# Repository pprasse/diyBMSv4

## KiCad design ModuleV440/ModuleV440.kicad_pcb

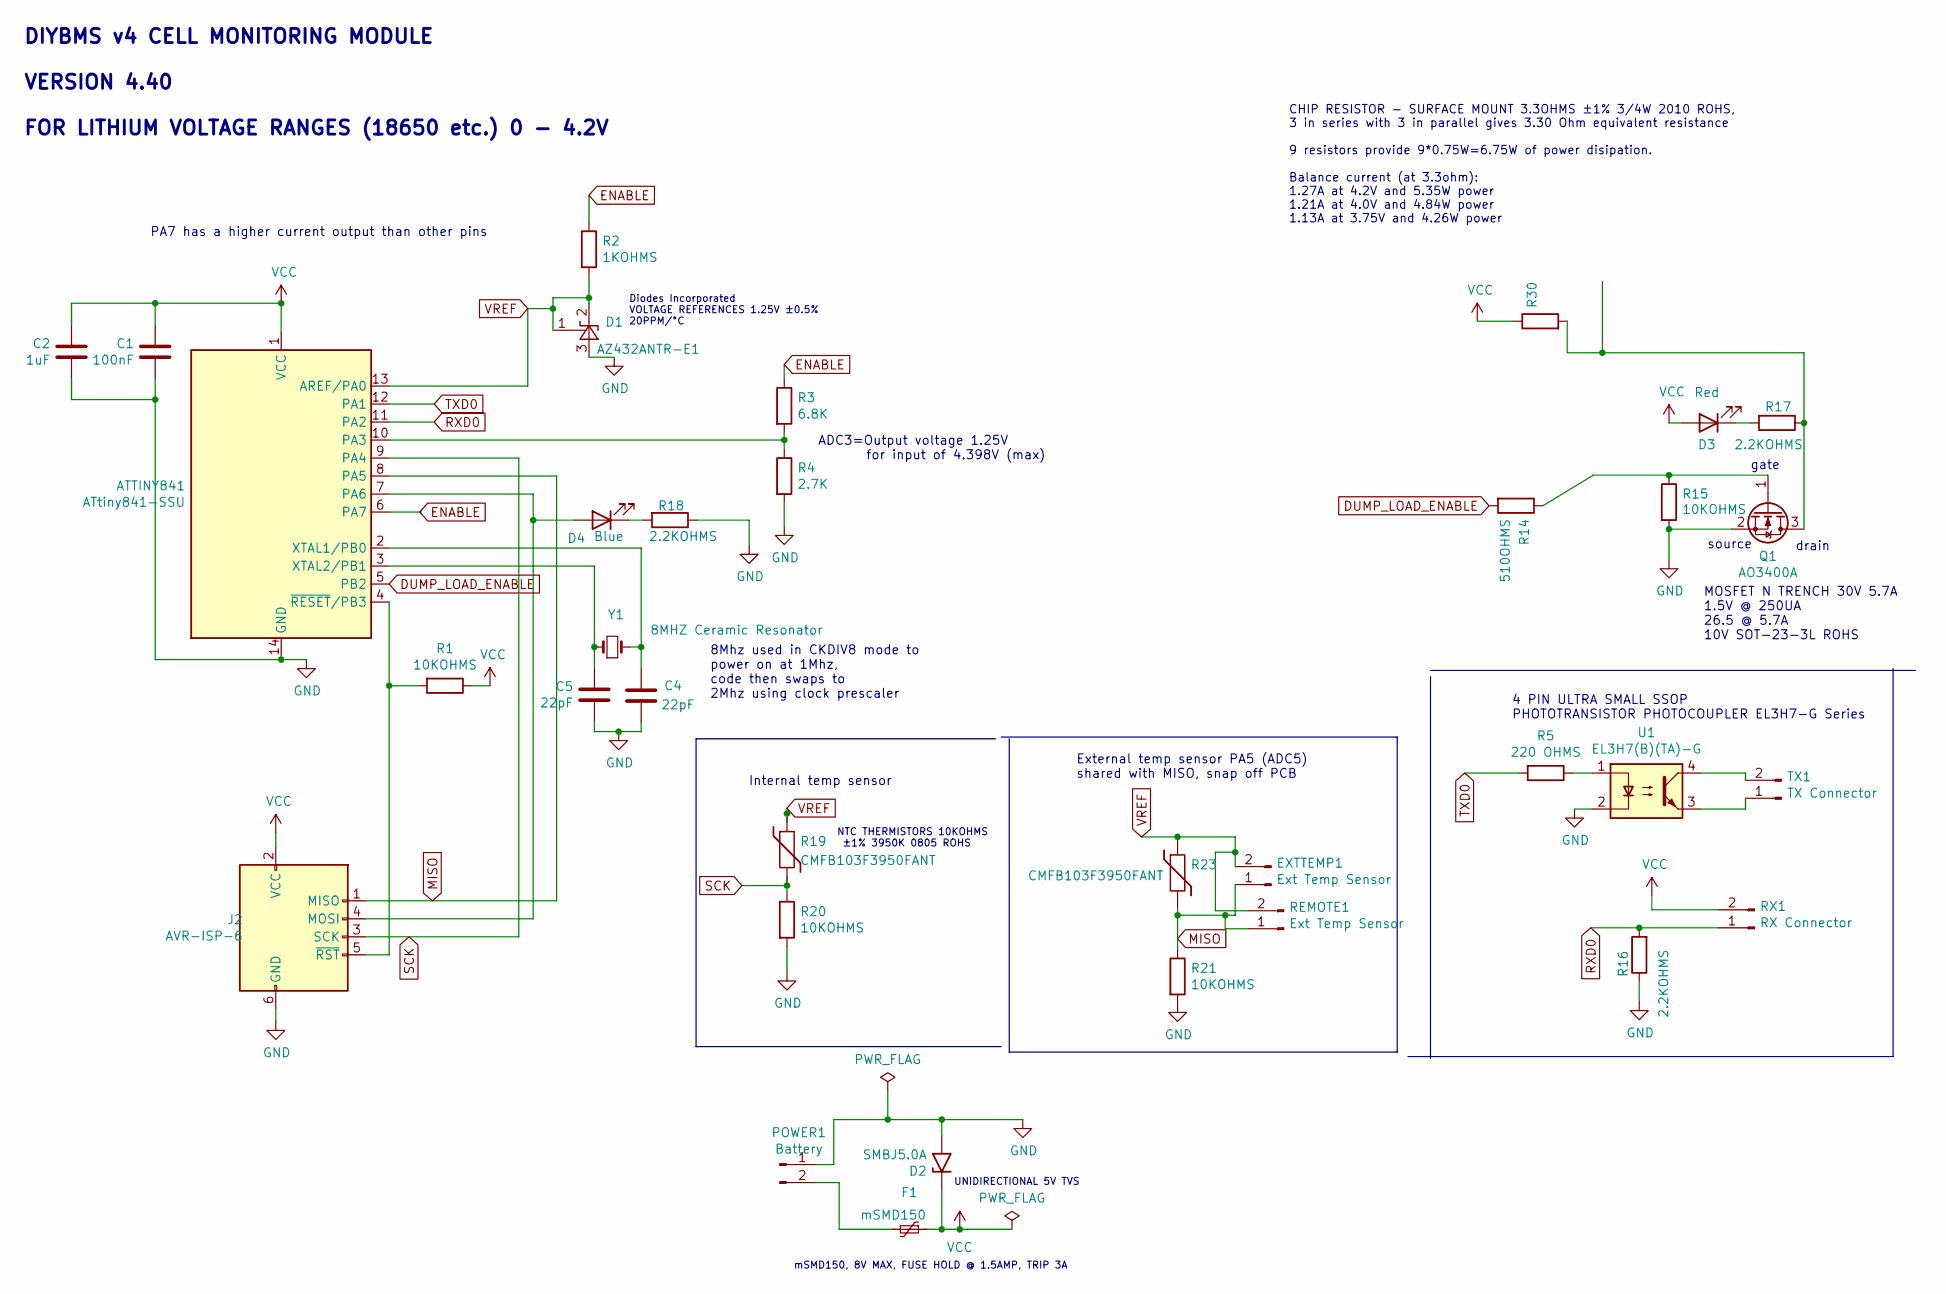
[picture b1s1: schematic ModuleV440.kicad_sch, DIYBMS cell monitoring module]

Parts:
ATTINY841: ATtiny841-SSU; SOIC-14_3.9x8.7mm_P1.27mm; LCSCStockCode C219103
C1: 100nF; C_0805_2012Metric; PartNumber CC0805KRX7R9BB104; LCSCStockCode C49678
C2: 1uF; C_0805_2012Metric; PartNumber CL21B105KBFNNNE; LCSCStockCode C28323
C4, C5: 22pF; C_0805_2012Metric; PartNumber CL21C220JBANNNC; LCSCStockCode C1804
D1: AZ432ANTR-E1; SOT-23; PartNumber AZ432ANTR-E1; LCSCStockCode C84139
D2: SMBJ5.0A; D_SMB; LCSCStockCode C440263
D3: Red; LED_0805_2012Metric; PartNumber 2012HRK-620D; LCSCStockCode C84256
D4: Blue; LED_0805_2012Metric; PartNumber Blue LED; LCSCStockCode C2293
EXTTEMP1: Ext Temp Sensor; JST_PH_S2B-PH-K_1x02_P2.00mm_Horizontal; PartNumber S2B-PH-K(LF)(SN); LCSCStockCode C265016
F1: mSMD150; Fuse_1812_4532Metric; PartNumber mSMD150; LCSCStockCode C70121
J2: AVR-ISP-6; Pin_Header_Straight_2x03_Pitch2.54mm; LCSCStockCode C65114
POWER1: Battery; JST_PH_S2B-PH-K_1x02_P2.00mm_Horizontal; PartNumber S2B-PH-K(LF)(SN); LCSCStockCode C265016
Q1: AO3400A; SOT-23; PartNumber AO3400A; LCSCStockCode C20917
R1, R15, R20, R21: 10KOHMS; R_0805_2012Metric; PartNumber 0805W8F1002T5E; LCSCStockCode C17414
R2: 1KOHMS; R_0805_2012Metric; PartNumber 0805W8F1001T5E; LCSCStockCode C17513
R3: 6.8K; R_0805_2012Metric; PartNumber 0805W8F6801T5E; LCSCStockCode C17772
R4: 2.7K; R_0805_2012Metric; PartNumber 0805W8F2701T5E; LCSCStockCode C17530
R5: 220 OHMS; R_0805_2012Metric; PartNumber 0805W8F2200T5E; LCSCStockCode C17557
R14: 510OHMS; R_0805_2012Metric; PartNumber 0805W8F5100T5E; LCSCStockCode C17734
R16, R17, R18: 2.2KOHMS; R_0805_2012Metric; PartNumber 0805W8F2201T5E; LCSCStockCode C17520
R19, R23: CMFB103F3950FANT; R_0805_2012Metric; PartNumber CMFB103F3950FANT; LCSCStockCode C51597
R30: 3.3OHM 3/4W; R_Radial_Power_L13.0mm_W9.0mm_P5.00mm; PartNumber SQMW53R3J
REMOTE1: Ext Temp Sensor; PinHeader_1x02_P2.54mm_Vertical
RX1: RX Connector; JST_PH_S2B-PH-K_1x02_P2.00mm_Horizontal; PartNumber S2B-PH-K(LF)(SN); LCSCStockCode C265016
TX1: TX Connector; JST_PH_S2B-PH-K_1x02_P2.00mm_Horizontal; PartNumber S2B-PH-K(LF)(SN); LCSCStockCode C265016
U1: EL3H7(B)(TA)-G; SOP-4_4.4x2.6mm_P1.27mm; PartNumber EL3H7(B)(TA)-G; LCSCStockCode C32565
Y1: 8MHZ Ceramic Resonator; Crystal_SMD_5032-2pin_5.0x3.2mm; PartNumber X50328MSB2GI; LCSCStockCode C115962

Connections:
DUMP_LOAD_ENABLE: ATTINY841.5 (PB2), R14.2
ENABLE: ATTINY841.6 (PA7), R2.1, R3.1
GND: ATTINY841.14 (GND), C1.2, C2.2, C4.2, C5.2, D1.3 (A), D2.2 (A2), J2.6 (GND), POWER1.1, Q1.2 (S), R4.2, R15.2, R16.1, R18.1, R20.2, R21.2, U1.2
MISO: ATTINY841.8 (PA5), EXTTEMP1.1, J2.1 (MISO), R21.1, R23.2, REMOTE1.1
unnamed: ATTINY841.10 (PA3), R3.2, R4.1
unnamed: ATTINY841.7 (PA6), D4.2 (A), J2.4 (MOSI)
unnamed: ATTINY841.2 (XTAL1/PB0), C4.1, Y1.2
unnamed: ATTINY841.3 (XTAL2/PB1), C5.1, Y1.1
unnamed: ATTINY841.4 (~RESET/PB3), J2.5 (~RST), R1.2
unnamed: D3.1 (K), R17.2
unnamed: D4.1 (K), R18.2
unnamed: F1.2, POWER1.2
unnamed: Q1.3 (D), R17.1, R30.2
unnamed: Q1.1 (G), R14.1, R15.1
unnamed: R5.1, U1.1
unnamed: TX1.1, U1.3
unnamed: TX1.2, U1.4
RXD0: ATTINY841.11 (PA2), R16.2, RX1.1
SCK: ATTINY841.9 (PA4), J2.3 (SCK), R19.2, R20.1
TXD0: ATTINY841.12 (PA1), R5.2
VCC: ATTINY841.1 (VCC), C1.1, C2.1, D2.1 (A1), D3.2 (A), F1.1, J2.2 (VCC), R1.1, R30.1, RX1.2
VREF: ATTINY841.13 (AREF/PA0), D1.1 (FB), D1.2 (K), EXTTEMP1.2, R2.2, R19.1, R23.1, REMOTE1.2

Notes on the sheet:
PA7 has a higher current output than other pins
CHIP RESISTOR - SURFACE MOUNT 3.3OHMS ±1% 3/4W 2010 ROHS, 3 in series with 3 in parallel gives 3.30 Ohm equivalent resistance 9 resistors provide 9*0.75W=6.75W of power disipation. Balance current (at 3.3ohm): 1.27A at 4.2V and 5.35W power 1.21A at 4.0V and 4.84W power 1.13A at 3.75V and 4.26W power
drain
mSMD150, 8V MAX, FUSE HOLD @ 1.5AMP, TRIP 3A
8Mhz used in CKDIV8 mode to power on at 1Mhz, code then swaps to 2Mhz using clock prescaler
4 PIN ULTRA SMALL SSOP PHOTOTRANSISTOR PHOTOCOUPLER EL3H7-G Series
ADC3=Output voltage 1.25V for input of 4.398V (max)
Diodes Incorporated VOLTAGE REFERENCES 1.25V ±0.5% 20PPM/°C
source
DIYBMS v4 CELL MONITORING MODULE VERSION 4.40 FOR LITHIUM VOLTAGE RANGES (18650 etc.) 0 - 4.2V
UNIDIRECTIONAL 5V TVS
NTC THERMISTORS 10KOHMS ±1% 3950K 0805 ROHS
gate
Internal temp sensor
External temp sensor PA5 (ADC5) shared with MISO, snap off PCB
MOSFET N TRENCH 30V 5.7A 1.5V @ 250UA 26.5 @ 5.7A 10V SOT-23-3L ROHS

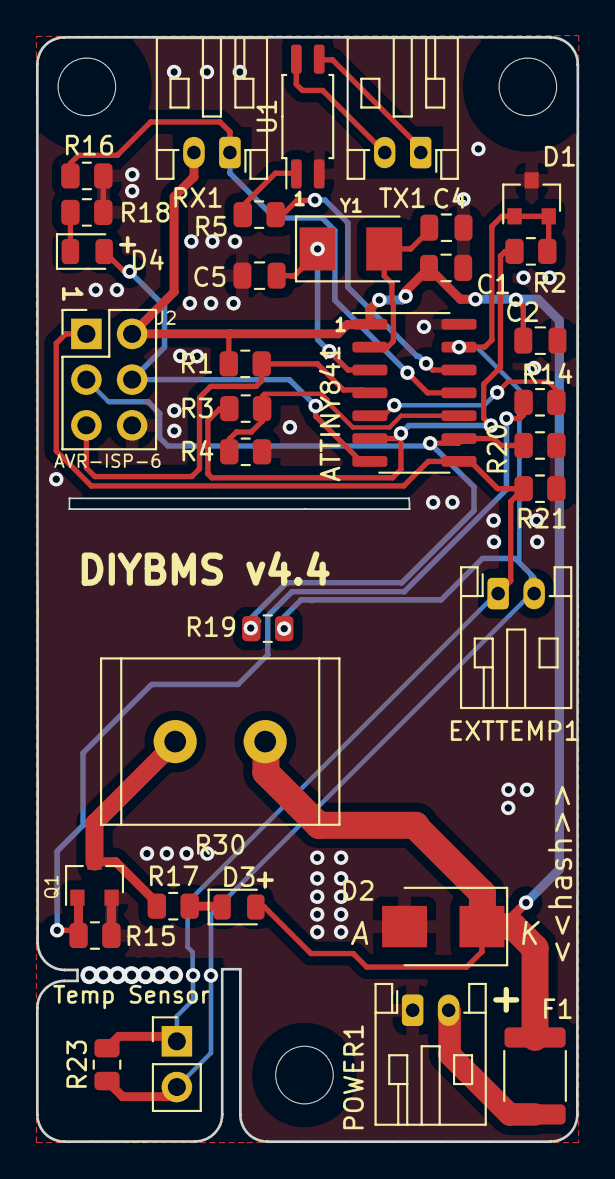
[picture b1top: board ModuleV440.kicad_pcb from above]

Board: 2 copper layers, 30.0 x 61.3 mm, 34 parts (0 on the bottom side), 22 nets.

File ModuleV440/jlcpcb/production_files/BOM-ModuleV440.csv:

Comment,Designator,Footprint,LCSC
8MHZ Ceramic Resonator,Y1,Crystal_SMD_5032-2pin_5.0x3.2mm,C115962
3.3OHM 3/4W,R30,R_Radial_Power_L13.0mm_W9.0mm_P5.00mm,C1366653
10KOHMS,"R1,R15,R20,R21",R_0805_2012Metric,C17414
1KOHMS,R2,R_0805_2012Metric,C17513
2.2KOHMS,"R16,R17,R18",R_0805_2012Metric,C17520
2.7K,R4,R_0805_2012Metric,C17530
220 OHMS,R5,R_0805_2012Metric,C17557
510OHMS,R14,R_0805_2012Metric,C17734
6.8K,R3,R_0805_2012Metric,C17772
22pF,"C4,C5",C_0805_2012Metric,C1804
AO3400A,Q1,SOT-23,C20917
ATtiny841-SSU,ATTINY841,SOIC-14_3.9x8.7mm_P1.27mm,C219103
Blue,D4,LED_0805_2012Metric,C2293
Ext Temp Sensor,"EXTTEMP1,POWER1,RX1,TX1",JST_PH_S2B-PH-K_1x02_P2.00mm_Horizontal,C265016
1uF,C2,C_0805_2012Metric,C28323
EL3H7(B)(TA)-G,U1,SOP-4_4.4x2.6mm_P1.27mm,C32565
SMBJ5.0A,D2,D_SMB,C440263
100nF,C1,C_0805_2012Metric,C49678
CMFB103F3950FANT,"R19,R23",R_0805_2012Metric,C51597
AVR-ISP-6,J2,Pin_Header_Straight_2x03_Pitch2.54mm,C65114
mSMD150,F1,Fuse_1812_4532Metric,C70121
AZ432ANTR-E1,D1,SOT-23,C84139
Red,D3,LED_0805_2012Metric,C84256
Ext Temp Sensor,REMOTE1,PinHeader_1x02_P2.54mm_Vertical,

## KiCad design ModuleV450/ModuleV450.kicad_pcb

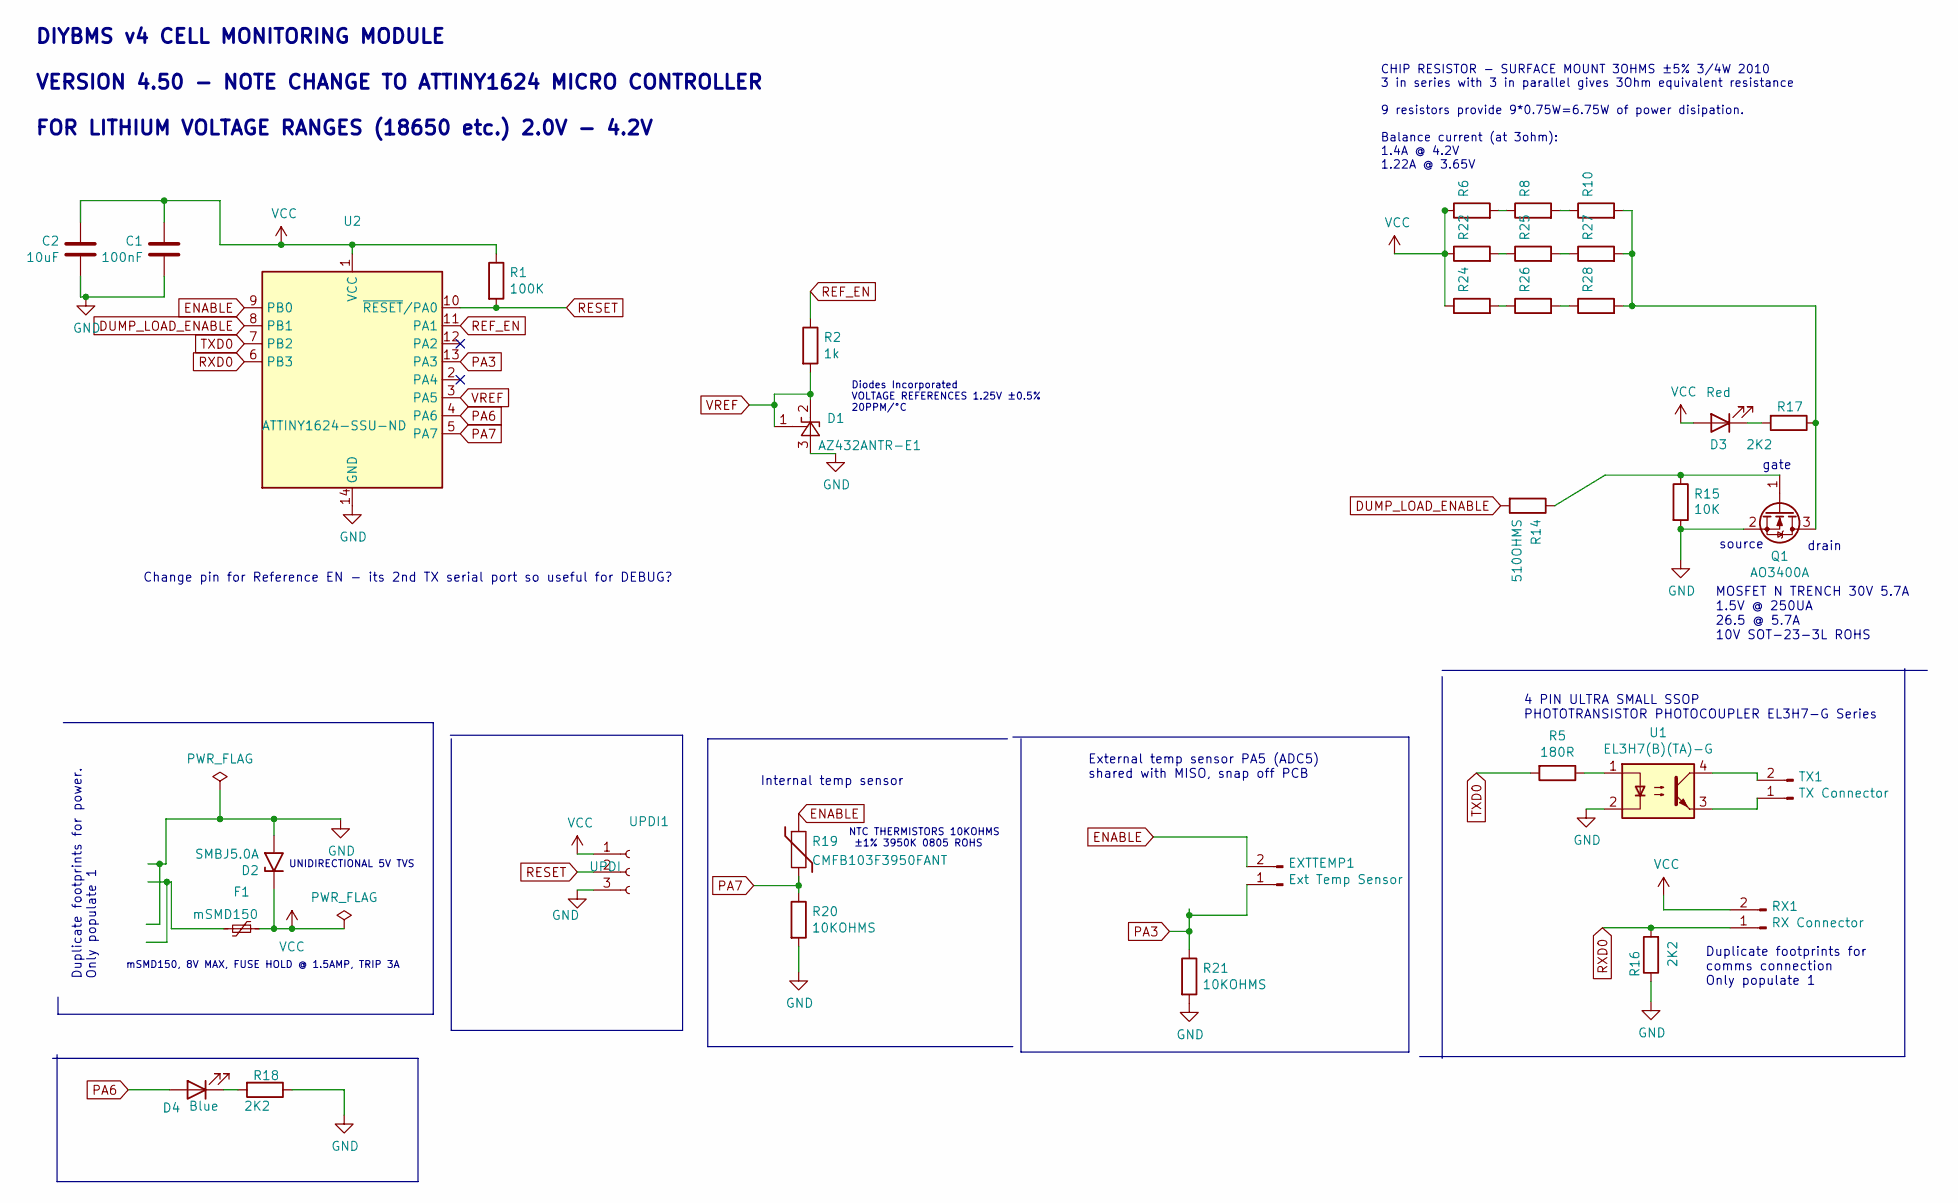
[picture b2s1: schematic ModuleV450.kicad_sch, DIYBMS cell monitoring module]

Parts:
C1: 100nF; C_0805_2012Metric; PartNumber CC0805KRX7R9BB104; LCSCStockCode C49678
C2: 10uF; C_0805_2012Metric; PartNumber CL21A106KAYNNNE; LCSCStockCode C15850
D1: AZ432ANTR-E1; SOT-23; PartNumber AZ432ANTR-E1; LCSCStockCode C84139
D2: SMBJ5.0A; D_SMB; LCSCStockCode C440263
D3: Red; LED_0805_2012Metric; PartNumber NCD0805R1; LCSCStockCode C84256
D4: Blue; LED_0603_1608Metric; PartNumber 19-217/GHC-YR1S2/3T; LCSCStockCode C72043
EXTTEMP1: Ext Temp Sensor; PinHeader_1x02_P2.54mm_Vertical; PartNumber S2B-PH-K(LF)(SN); LCSCStockCode C265016
F1: mSMD150; Fuse_1812_4532Metric; PartNumber mSMD150; LCSCStockCode C70121
Q1: AO3400A; SOT-23; PartNumber AO3400A; LCSCStockCode C347475
R1: 100K; R_0805_2012Metric; PartNumber 0805W8F1003T5E; LCSCStockCode C149504
R2: 1k; R_0805_2012Metric; PartNumber 0805W8F1001T5E; LCSCStockCode C17513
R5: 180R; R_0805_2012Metric; PartNumber 0805W8F1800T5E; LCSCStockCode C25270
R6, R8, R10, R22, R24, R25, R26, R27, R28: 3R; R_2010_5025Metric; PartNumber 201007J030JT4E; LCSCStockCode C474300
R14: 510OHMS; R_0805_2012Metric; PartNumber 0805W8F5100T5E; LCSCStockCode C17734
R15: 10K; R_0805_2012Metric; PartNumber 0805W8F1002T5E; LCSCStockCode C17414
R16, R17, R18: 2K2; R_0805_2012Metric; PartNumber 0805W8F2201T5E; LCSCStockCode C17520
R19: CMFB103F3950FANT; R_0805_2012Metric; PartNumber CMFB103F3950FANT; LCSCStockCode C51597
R20, R21: 10KOHMS; R_0805_2012Metric; PartNumber 0805W8F1002T5E; LCSCStockCode C17414
RX1: RX Connector; PinHeader_1x02_P2.54mm_Horizontal; PartNumber PZ254R-11-02P; LCSCStockCode C492410
TX1: TX Connector; PinHeader_1x02_P2.54mm_Horizontal; PartNumber PZ254R-11-02P; LCSCStockCode C492410
U1: EL3H7(B)(TA)-G; SOP-4_4.4x2.6mm_P1.27mm; PartNumber EL3H7(B)(TA)-G; LCSCStockCode C32565
U2: ATTINY1624-SSU-ND; SOIC-14_3.9x8.7mm_P1.27mm; PartNumber ATTINY1624-SSU-ND; LCSCStockCode C3237666
UPDI1: UPDI; PinSocket_1x03_P2.54mm_Vertical

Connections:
DUMP_LOAD_ENABLE: R14.2, U2.8 (PB1)
ENABLE: EXTTEMP1.2, R19.1, U2.9 (PB0)
GND: C1.2, C2.2, D1.3 (A), D2.2 (A2), Q1.2 (S), R15.2, R16.1, R18.1, R20.2, R21.2, U1.2, U2.14 (GND), UPDI1.3
unnamed: D3.1 (K), R17.2
unnamed: D4.1 (K), R18.2
unnamed 5: Q1.3 (D), R10.2, R17.1, R27.2, R28.2; also elsewhere on the board
unnamed: Q1.1 (G), R14.1, R15.1
unnamed: R5.1, U1.1
unnamed: R6.2, R8.1
unnamed: R8.2, R10.1
unnamed: R22.2, R25.1
unnamed: R24.2, R26.1
unnamed: R25.2, R27.1
unnamed: R26.2, R28.1
unnamed: TX1.1, U1.3
unnamed: TX1.2, U1.4
PA3: EXTTEMP1.1, R21.1, U2.13 (PA3)
PA6: D4.2 (A), U2.4 (PA6)
PA7: R19.2, R20.1, U2.5 (PA7)
REF_EN: R2.1, U2.11 (PA1)
RESET: R1.2, U2.10 (~RESET/PA0), UPDI1.2
RXD0: R16.2, RX1.1, U2.6 (PB3)
TXD0: R5.2, U2.7 (PB2)
VCC: C1.1, C2.1, D2.1 (A1), D3.2 (A), F1.1, R1.1, R6.1, R22.1, R24.1, RX1.2, U2.1 (VCC), UPDI1.1; also elsewhere on the board
VREF: D1.1 (FB), D1.2 (K), R2.2, U2.3 (PA5)

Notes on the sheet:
drain
4 PIN ULTRA SMALL SSOP PHOTOTRANSISTOR PHOTOCOUPLER EL3H7-G Series
gate
UNIDIRECTIONAL 5V TVS
MOSFET N TRENCH 30V 5.7A 1.5V @ 250UA 26.5 @ 5.7A 10V SOT-23-3L ROHS
External temp sensor PA5 (ADC5) shared with MISO, snap off PCB
Change pin for Reference EN - its 2nd TX serial port so useful for DEBUG?
DIYBMS v4 CELL MONITORING MODULE VERSION 4.50 - NOTE CHANGE TO ATTINY1624 MICRO CONTROLLER FOR LITHIUM VOLTAGE RANGES (18650 etc.) 2.0V - 4.2V
source
Duplicate footprints for comms connection Only populate 1
NTC THERMISTORS 10KOHMS ±1% 3950K 0805 ROHS
CHIP RESISTOR - SURFACE MOUNT 3OHMS ±5% 3/4W 2010 3 in series with 3 in parallel gives 3Ohm equivalent resistance 9 resistors provide 9*0.75W=6.75W of power disipation. Balance current (at 3ohm): 1.4A @ 4.2V 1.22A @ 3.65V
mSMD150, 8V MAX, FUSE HOLD @ 1.5AMP, TRIP 3A
Internal temp sensor
Diodes Incorporated VOLTAGE REFERENCES 1.25V ±0.5% 20PPM/°C
Duplicate footprints for power. Only populate 1

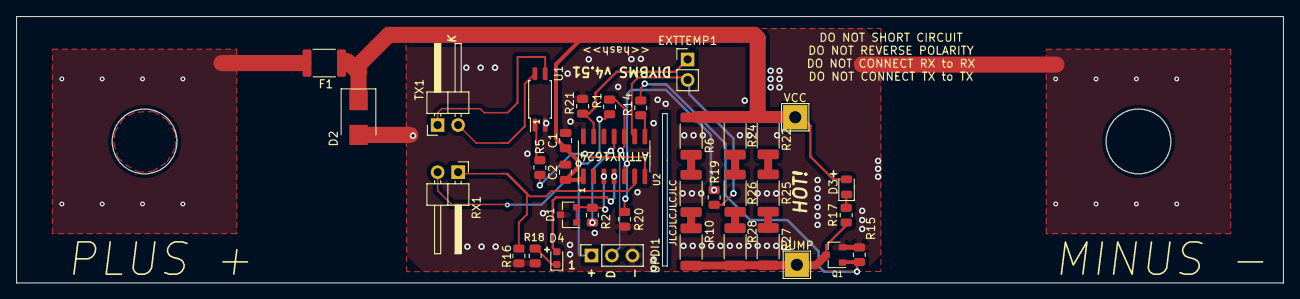
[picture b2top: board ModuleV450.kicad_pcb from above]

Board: 2 copper layers, 157.0 x 33.0 mm, 36 parts (0 on the bottom side), 25 nets.

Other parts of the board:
DUMP: TestPoint_THTPad_3.0x3.0mm_Drill1.5mm
VCC: TestPoint_THTPad_3.0x3.0mm_Drill1.5mm

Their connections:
unnamed 5: DUMP.1; also elsewhere on the board
VCC: VCC.1; also elsewhere on the board

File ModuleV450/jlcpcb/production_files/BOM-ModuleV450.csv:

Comment,Designator,Footprint,LCSC
100K,R1,R_0805_2012Metric,C149504
10uF,C2,C_0805_2012Metric,C15850
3R,"R10,R22,R24,R25,R26,R27,R28,R6,R8",R_2010_5025Metric,C159239
10K,"R15,R20,R21",R_0805_2012Metric,C17414
1k,R2,R_0805_2012Metric,C17513
2K2,"R16,R17,R18",R_0805_2012Metric,C17520
510OHMS,R14,R_0805_2012Metric,C17734
180R,R5,R_0805_2012Metric,C25270
EL3H7(B)(TA)-G,U1,SOP-4_4.4x2.6mm_P1.27mm,C32565
AO3400A,Q1,SOT-23,C347475
SMBJ5.0A,D2,D_SMB,C440263
AZ432ANTR-E1,D1,SOT-23,C460576
RX Connector,"RX1,TX1",PinHeader_1x02_P2.54mm_Horizontal,C492410
100nF,C1,C_0805_2012Metric,C49678
UPDI,UPDI1,PinSocket_1x03_P2.54mm_Vertical,C5116529
CMFB103F3950FANT,R19,R_0805_2012Metric,C51597
ATTINY1624-SSU-ND,U2,SOIC-14_3.9x8.7mm_P1.27mm,C5160891
mSMD150,F1,Fuse_1812_4532Metric,C70121
Blue,D4,LED_0603_1608Metric,C72043
Red,D3,LED_0805_2012Metric,C84256

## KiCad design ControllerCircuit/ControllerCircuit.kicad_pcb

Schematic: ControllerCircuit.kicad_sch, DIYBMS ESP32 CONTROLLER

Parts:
C1, C2, C6, C8, C9: 100nF; C_0805_2012Metric; LCSCStockCode C49678
C3, C4: 22uF 6.3V; CP_EIA-3216-18_Kemet-A_Pad1.58x1.35mm_HandSolder; PartNumber TC212A226K006Y; LCSCStockCode C110786
C5: 22uF; C_1206_3216Metric; PartNumber CL31A226KPHNNNE; LCSCStockCode C5672
C7, C11: 1uF; C_0805_2012Metric; LCSCStockCode C28323
C10, C13: 1uF; C_0805_2012Metric; PartNumber CL21B105KBFNNNE; LCSCStockCode C28323
C12: 0.1uF-100V; C_0805_2012Metric; PartNumber C0805C104K1RECAUTO; LCSCStockCode C696367
C14: 100nF; C_0805_2012Metric; PartNumber CC0805KRX7R9BB104; LCSCStockCode C49678
D1: RGB; LED_RGB_5050-6; LCSCStockCode C219409
D2, D5: LL4148; D_MiniMELF; PartNumber LL4148; LCSCStockCode C9808
D3, D4: YELLOW LED; LED_0603_1608Metric_Pad1.05x0.95mm_HandSolder; LCSCStockCode C72038
D6: MHPC3528CRGBCT; LED_MHPC3528CRGBCT
D8: NUP2105LT1G; SOT-23; LCSCStockCode C2976509
F1: Fuse, 1.85A; Fuse_2920_7451Metric; PartNumber TLC-LSMD185; LCSCStockCode C262041
J1, J4, J7, J12: ScrewTerminal; Terminal-Block_3.81_4P_LCSC_C395880; LCSCStockCode C395880
J2, J3: ScrewTerminal3Pin; Terminal-Block_5.0mm_3P-LCSC_C395850; LCSCStockCode C395850
J5: ScrewTerminal; Terminal-Block_3.81_2P-LCSC_C395878; LCSCStockCode C395878
J8: 2x3 2.54mm IDC Connectors; PinHeader_2x03_P2.54mm_Vertical; LCSCStockCode C132438
J9: Shunt; Terminal-Block_3.81_4P_LCSC_C395880; LCSCStockCode C395880
J10: Conn_01x02_Female; PinHeader_1x02_P2.54mm_Horizontal; LCSCStockCode C376120
J14: Unused header; PinHeader_1x07_P2.54mm_Vertical
J15: Molex 0472192001; 0472192001; Manufacturer_Part_Number 0472192001; Mouser Part Number N/A
JP1: OptTermination; SolderJumper-2_P1.3mm_Bridged_Pad1.0x1.5mm
JP4: OptTermination; SolderJumper-2_P1.3mm_Bridged_RoundedPad1.0x1.5mm
K1, K2: SRD-05VDC-SL-C; RELAY_SRD-05VDC-SL-C; PartNumber SRD-05VDC-SL-C; LCSCStockCode C35449
LCD1: LCD; TFTSPI_2_8_240x320_TOUCH; LCSCStockCode C52711/C358718
Q1, Q2, Q4: AO3400A; SOT-23; PartNumber AO3400A; LCSCStockCode C344010
Q3: AO3401A; SOT-23; LCSCStockCode C15127
R1, R17, R18, R21, R25: 220R; R_0805_2012Metric; PartNumber 0805W8F2200T5E; LCSCStockCode C17557
R2, R5, R16: 2K2; R_0805_2012Metric; PartNumber 0805W8F2201T5E; LCSCStockCode C17520
R3: 180R; R_0805_2012Metric; PartNumber 0805W8F1800T5E; LCSCStockCode C25270
R4, R10, R12, R13, R14: 560R; R_0805_2012Metric; PartNumber 0805W8F5600T5E; LCSCStockCode C28636
R6, R8, R9: 120R; R_0805_2012Metric; PartNumber 0805W8F1200T5E; LCSCStockCode C17437
R7, R11, R15, R27: 51K; R_0805_2012Metric; PartNumber 0805W8F5102T5E; LCSCStockCode C17737
R19, R22, R29, R31, R32: 10K; R_0805_2012Metric; PartNumber 0805W8F1002T5E; LCSCStockCode C17414
R20: 1M; R_0805_2012Metric; PartNumber 0805W8F1004T5E; LCSCStockCode C17514
R23, R30: 10R; R_0805_2012Metric; PartNumber 0805W8F100JT5E; LCSCStockCode C17415
R24, R26, R28: 22K; R_0805_2012Metric; PartNumber 0805W8F2202T5E; LCSCStockCode C17560
RX1: Receive; JST_PH_S2B-PH-K_1x02_P2.00mm_Horizontal; PartNumber S2B-PH-K-S-GW; LCSCStockCode C157932
SW1, SW2: SW_Push; SW_PUSH_6mm_H5mm; PartNumber XUNPU TS-1002-10026; LCSCStockCode C455101
TX1: Transmit; JST_PH_S2B-PH-K_1x02_P2.00mm_Horizontal; PartNumber S2B-PH-K-S-GW; LCSCStockCode C157932
U1: TXS0102DCU; VSSOP-8_2.3x2mm_P0.5mm; LCSCStockCode C53434
U2: EL3H7(B)(TA)-G; SOP-4_4.4x2.6mm_P1.27mm; LCSCStockCode C32565
U3: TCA6416APWR; TSSOP-24_4.4x7.8mm_P0.65mm; LCSCStockCode C130203
U4: ESP32-DEVKITC-32D; MODULE_ESP32-DEVKITC-32D; LCSCStockCode C319202/C319202
U5: SN65HVD75DR; SOIC-8_3.9x4.9mm_P1.27mm; PartNumber SN65HVD75DR; LCSCStockCode C57928
U6: AMS1117-3.3; SOT-223-3_TabPin2; PartNumber AMS1117-3.3; LCSCStockCode C6186
U7: SN65HVD1050D; SOIC-8_3.9x4.9mm_P1.27mm; LCSCStockCode C14019
U8: INA229; VSSOP-10_3x3mm_P0.5mm; PartNumber INA229AIDGSR; LCSCStockCode C2846803
U9, U12: AQY282SX; SO-4_4.4x3.6mm_P2.54mm; LCSCStockCode C250827

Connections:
+5V: F1.2, J5.1
/AVRISP_RESET: J8.5 (~RST), U4.33 (IO0)
/BLUE_LED: R1.2, U3.13 (P10)
/CANBUS_RX: U1.4 (A2), U4.30 (IO17)
/CANBUS_TX: U1.5 (A1), U4.31 (IO16)
/DISPLAY_DC: LCD1.10 (D/C), U4.35 (IO15)
/DISPLAY_LED: R21.2, U3.16 (P13)
/EXT_IO_A: J4.1, U3.4 (P0)
/EXT_IO_B: J4.2, U3.5 (P1)
/EXT_IO_C: J4.3, U3.6 (P2)
/EXT_IO_D: J4.4, U3.7 (P3)
/GREEN_LED: R17.2, U3.15 (P12)
/HSPI_CLK: LCD1.8 (SCK), U4.12 (IO14)
/HSPI_MISO: LCD1.6 (MISO), U4.13 (IO12)
/HSPI_MOSI: LCD1.9 (MOSI), U4.15 (IO13)
/IO2: Q4.3 (D), R20.1, U4.34 (IO2)
/IO4: LCD1.4 (T_CS), U4.32 (IO4)
/IO5: J15.2 (CD/DAT3), LCD1.SD4 (SD_CS), R22.1, U4.29 (IO5)
/IO21: U4.25 (IO21), U5.1 (R)
/IO22: U4.22 (IO22), U5.4 (D)
/IO25: U4.9 (IO25), U5.2 (RE), U5.3 (DE)
/IO26: R5.1, U3.22 (SCL), U4.10 (IO26)
/IO27: R16.1, U3.23 (SDA), U4.11 (IO27)
/IO32: R3.2, U4.7 (IO32)
/IO33: R31.1, U4.8 (IO33), U8.1 (CS)
/IO34_INPUT: J14.4, U4.5 (IO34)
/IO35_INPUT: R32.2, U4.6 (IO35), U8.3 (~Alert)
/IO36_INPUT: LCD1.1 (T_IRQ), U4.3 (SENSOR_VP)
/IO39_INPUT: R19.1, U3.1 (~INT), U4.4 (SENSOR_VN)
/RED_LED: R4.2, U3.14 (P11)
/RELAY1: R10.2, U3.8 (P4)
/RELAY2: R14.2, U3.9 (P5)
/RELAY3_SSR: R18.2, U3.10 (P6)
/RELAY4_SSR: R25.2, U3.11 (P7)
/RESET: LCD1.11 (RESET), R29.1, U3.3 (~RESET), U4.2 (EN)
/SW1EXT: J14.5, R7.1, R26.2, SW1.1
/SW1OUTPUT: C7.1, R26.1, U3.17 (P14)
/SW2EXT: J14.6, R27.1, R28.2, SW2.1
/SW2OUTPUT: C11.1, R28.1, U3.19 (P16)
/VSPI_CLK: J8.3 (SCK), J15.5 (CLK), LCD1.5 (T_CLK), LCD1.SD1 (SD_SCK), U4.28 (IO18), U8.5 (SCLK)
/VSPI_MISO: J8.1 (MISO), J15.7 (DAT0), LCD1.2 (T_DO), LCD1.SD2 (SD_MISO), U4.27 (IO19), U8.4 (MISO)
/VSPI_MOSI: J8.4 (MOSI), J15.3 (CMD), LCD1.3 (T_DIN), LCD1.SD3 (SD_MOSI), U4.21 (IO23), U8.2 (MOSI)
FUSED5V: C2.1, C3.1, C5.2, C9.1, D2.1 (K), D5.1 (K), J1.1, J7.1, K1.A1, K2.A1, Q3.2 (S), R7.2, R12.2, R13.2, R24.2, R27.2, U1.7 (VCCB), U3.21 (ADDR), U3.24 (VCCP), U4.19 (EXT_5V), U6.3 (VI), U7.3 (VCC)
GND: C1.2, C2.2, C3.2, C4.2, C5.1, C6.2, C7.2, C8.1, C9.2, C10.2, C11.2, C13.1, C14.1, D1.4 (BA), D1.5 (GA), D1.6 (RA), D6.4, D8.3 (A), J1.4, J5.2, J7.2, J8.6 (GND), J10.2, J14.7, J15.6 (VSS), J15.G1 (GND_1), J15.G2 (GND_2), J15.G3 (GND_3), J15.G4 (GND_4), LCD1.12 (CS), LCD1.13 (GND), Q1.2 (S), Q2.2 (S), Q4.2 (S), R8.2, R11.1, R15.1, RX1.1, SW1.2, SW2.2, U1.2 (GND), U2.2, U3.12 (GND), U4.14 (GND1), U4.20 (GND3), U4.26 (GND2), U5.5 (GND), U6.1 (GND), U7.2 (GND), U7.8 (S), U8.7 (GND), U9.2, U12.2
unnamed: C12.1, R23.1, U8.10 (Vin+)
unnamed: C12.2, R30.1, U8.9 (Vin-)
unnamed: D1.1 (RK), D6.3, R17.1
unnamed: D1.2 (GK), D6.1, R4.1
unnamed: D1.3 (BK), D6.2, R1.1
unnamed: D2.2 (A), D3.1 (K), K1.A2, Q1.3 (D)
unnamed: D3.2 (A), R12.1
unnamed: D4.1 (K), D5.2 (A), K2.A2, Q2.3 (D)
unnamed: D4.2 (A), R13.1
unnamed: D8.1 (K), J7.4, JP1.1 (A), U7.6 (CANL)
unnamed: D8.2 (K), J7.3, R6.2, U7.7 (CANH)
unnamed: F1.1, Q3.3 (D)
unnamed: J1.2, R9.1, U5.6 (A)
unnamed: J1.3, JP4.1 (A), U5.7 (B)
unnamed: J2.1, K1.COM
unnamed: J2.2, K1.NC
unnamed: J2.3, K1.NO
unnamed: J3.1, K2.COM
unnamed: J3.2, K2.NC
unnamed: J3.3, K2.NO
unnamed: J9.1, R30.2
unnamed: J9.2, R23.2
unnamed: J9.4, U8.8 (Vbus)
unnamed: J10.1, R24.1, U3.20 (P17)
unnamed: J12.1, U9.3
unnamed: J12.2, U9.4
unnamed: J12.3, U12.3
unnamed: J12.4, U12.4
unnamed: JP1.2 (B), R6.1
unnamed: JP4.2 (B), R9.2
unnamed: LCD1.7 (LED), R21.1
unnamed: Q1.1 (G), R10.1, R11.2
unnamed: Q2.1 (G), R14.1, R15.2
unnamed: Q3.1 (G), R8.1
unnamed: Q4.1 (G), R2.1, RX1.2
unnamed: R3.1, U2.1
unnamed: R18.1, U9.1
unnamed: R25.1, U12.1
unnamed: TX1.1, U2.3
unnamed: TX1.2, U2.4
unnamed: U1.1 (B2), U7.4 (RXD)
unnamed: U1.8 (B1), U7.1 (TXD)

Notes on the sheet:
PIN 1 is an output (received data). RS485 half duplex IC required.
ILI9341
Provides 5V I/O pins for external interfaces and relays, up to 10mA per port. i2c address 0x21 (ADDR is high)
Power input
CANBUS
Standard Module comms
BATTERY+
The pins GPIO16 and GPIO17 are available for use only on the boards with the modules ESP32-WROOM and ESP32-SOLO-1. The boards with ESP32-WROVER modules have the pins reserved for internal use.
1=USB SERIAL 3=USB SERIAL 6=N/A 7=N/A 8=N/A 9=[NOT AVAILABE ON DEVKIT] mapped to IO16 on DEVKIT 10=[NOT AVAILABE ON DEVKIT] mapped to IO17 on DEVKIT 11=N/A 12=DISPLAY HSPI MISO / MTDI/GPIO12: internal pull-down 13=DISPLAY HSPI MOSI 14=DISPLAY HSPI CLK 16=SEE IO9 17=SEE IO10 18= VSPI_CLK (CONFIRMED)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
This work is licensed under a Creative Commons Attribution-NonCommercial-ShareAlike 2.0 UK: England & Wales License. https://creativecommons.org/licenses/by-nc-sa/2.0/uk/ You are free to: Share — copy and redistribute the material in any medium or format Adapt — remix, transform, and build upon the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
VBUS
120R optional resistor for termination, CONNECTED by default
Connected to USB port
LCD SCREEN = 42mA (including backlight @ 2.5mA)
Emergency stop button (pulled high)
ESP32 Strapping Pins GPIO0, GPIO5 and GPIO15 have pull-up resistors enabled during power up. GPIO2 and GPIO12 have pull-down resistors enabled during power up. These pull-up and pull-down resistors can be disabled via software once the device is running. The ESP32 will enter the serial bootloader w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
Panasonic AQY282SX Solid State Relay 60V 500mA AC or DC
MICRO SD CARD
Flyback diode calc Relay, 5VDC = 72mA 70ohm+/-10% 0.36W LL4148, Peak Reverse Voltage 100V Peak Fwd Surge Current 0.5A @1s, 1A@1ms Power Dissipation 500mW
DUAL FOOT PRINT - ONLY FIT 1 LED!
LCSC C2962096
Push buttons with de-bounce
Changes: CANBUS_S has been removed, hard wired to low LED output resistor values changed to cater for 5v
CHARGER/LOAD
POWER CONSUMPTION
Display is only item on bus so no CS needed
IO34 used on previous controller versions as TCA9534A_INTERRUPT_PIN
120R optional resistor for CAN termination, CONNECTED by default
i2c pull up resistors
Non-Commercial — You may not use the material for commercial purposes.
PIN MAPPING
Reverse polarity protection
Consider using part C8387 WJ15EDGRC-3.81-2P Pluggable System Terminal Block 3.81mm
Green/Red intentionally swapped to match component + ground! (foot print wrong)
RS-485
Using 4 pin connector to reduce part count
ONBOARD CURRENT SHUNT/MONITOR

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
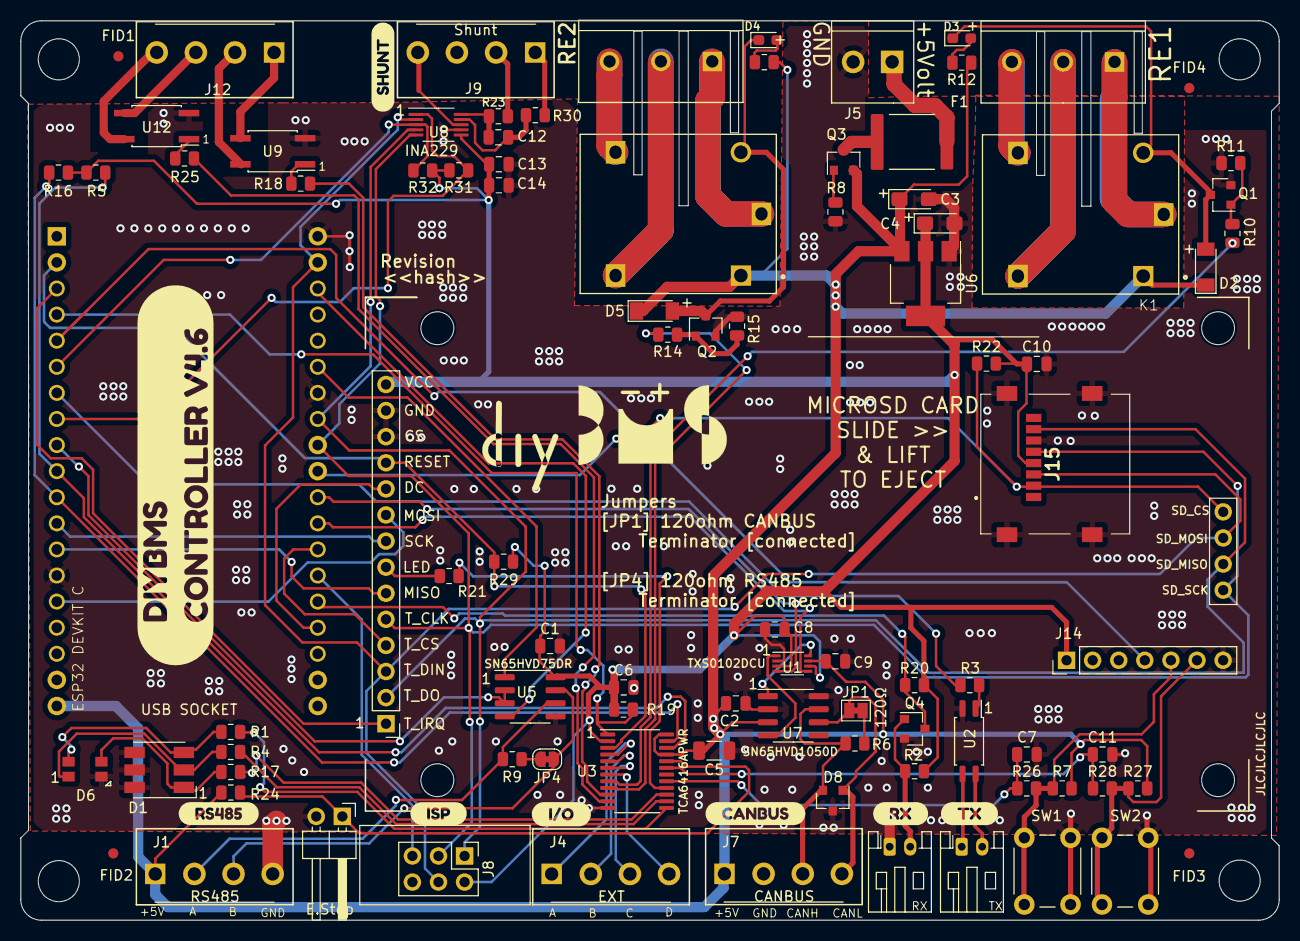
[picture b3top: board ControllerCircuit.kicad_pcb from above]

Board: 2 copper layers, 122.5 x 87.5 mm, 102 parts (1 on the bottom side), 87 nets.

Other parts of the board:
FID1, FID2, FID3, FID4: Fiducial_1mm_Mask2mm
e: LOGO; logo
svg2mod, svg2mod#2, svg2mod#3, svg2mod#4, svg2mod#5, svg2mod#6, svg2mod#7, svg2mod#8: G***; label

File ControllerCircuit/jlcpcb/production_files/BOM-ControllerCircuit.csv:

Comment,Designator,Footprint,LCSC
Molex 0472192001,J15,0472192001,
ESP32-DEVKITC-32D,U4,MODULE_ESP32-DEVKITC-32D,
INA229,U8,VSSOP-10_3x3mm_P0.5mm,
10K,R32,R_0805_2012Metric,
10K,R31,R_0805_2012Metric,
10R,R30,R_0805_2012Metric,
10R,R23,R_0805_2012Metric,
Shunt,J9,Terminal-Block_3.81_4P_LCSC_C395880,
100nF,C14,C_0805_2012Metric,
1uF,C13,C_0805_2012Metric,
0.1uF-100V,C12,C_0805_2012Metric,
ScrewTerminal,J5,Terminal-Block_3.81_2P-LCSC_C395878,
10K,R22,R_0805_2012Metric,
MHPC3528CRGBCT,D6,LED_MHPC3528CRGBCT,
SN65HVD1050D,U7,SOIC-8_3.9x4.9mm_P1.27mm,
TXS0102DCU,U1,VSSOP-8_2.3x2mm_P0.5mm,
100nF,C9,C_0805_2012Metric,
100nF,C8,C_0805_2012Metric,
SN65HVD75DR,U5,SOIC-8_3.9x4.9mm_P1.27mm,
Unused header,J14,PinHeader_1x07_P2.54mm_Vertical,
TCA6416APWR,U3,TSSOP-24_4.4x7.8mm_P0.65mm,
Fiducial_1mm_Mask2mm,FID4,Fiducial_1mm_Mask2mm,
Fiducial_1mm_Mask2mm,FID3,Fiducial_1mm_Mask2mm,
Fiducial_1mm_Mask2mm,FID2,Fiducial_1mm_Mask2mm,
Fiducial_1mm_Mask2mm,FID1,Fiducial_1mm_Mask2mm,
10K,R29,R_0805_2012Metric,
22uF,C5,C_1206_3216Metric,
1M,R20,R_0805_2012Metric,
AO3400A,Q4,SOT-23,
"Fuse, 1.85A",F1,Fuse_2920_7451Metric,
SW_Push,SW2,SW_PUSH_6mm_H5mm,
22K,R28,R_0805_2012Metric,
51K,R27,R_0805_2012Metric,
1uF,C11,C_0805_2012Metric,
SW_Push,SW1,SW_PUSH_6mm_H5mm,
22K,R26,R_0805_2012Metric,
51K,R7,R_0805_2012Metric,
1uF,C7,C_0805_2012Metric,
YELLOW LED,D4,LED_0603_1608Metric_Pad1.05x0.95mm_HandSolder,
YELLOW LED,D3,LED_0603_1608Metric_Pad1.05x0.95mm_HandSolder,
LL4148,D5,D_MiniMELF,
LL4148,D2,D_MiniMELF,
LCD,LCD1,TFTSPI_2_8_240x320_TOUCH,
NUP2105LT1G,D8,SOT-23,
ScrewTerminal,J12,Terminal-Block_3.81_4P_LCSC_C395880,
AQY282SX,U12,SO-4_4.4x3.6mm_P2.54mm,
220R,R25,R_0805_2012Metric,
AQY282SX,U9,SO-4_4.4x3.6mm_P2.54mm,
AMS1117-3.3,U6,SOT-223-3_TabPin2,
EL3H7(B)(TA)-G,U2,SOP-4_4.4x2.6mm_P1.27mm,
Transmit,TX1,JST_PH_S2B-PH-K_1x02_P2.00mm_Horizontal,
Receive,RX1,JST_PH_S2B-PH-K_1x02_P2.00mm_Horizontal,
22K,R24,R_0805_2012Metric,
220R,R21,R_0805_2012Metric,
10K,R19,R_0805_2012Metric,
220R,R18,R_0805_2012Metric,
220R,R17,R_0805_2012Metric,
2K2,R16,R_0805_2012Metric,
51K,R15,R_0805_2012Metric,
560R,R14,R_0805_2012Metric,
560R,R13,R_0805_2012Metric,
560R,R12,R_0805_2012Metric,
51K,R11,R_0805_2012Metric,
560R,R10,R_0805_2012Metric,
120R,R9,R_0805_2012Metric,
120R,R8,R_0805_2012Metric,
120R,R6,R_0805_2012Metric,
2K2,R5,R_0805_2012Metric,
560R,R4,R_0805_2012Metric,
180R,R3,R_0805_2012Metric,
2K2,R2,R_0805_2012Metric,
220R,R1,R_0805_2012Metric,
AO3401A,Q3,SOT-23,
AO3400A,Q2,SOT-23,
AO3400A,Q1,SOT-23,
Conn_01x02_Female,J10,PinHeader_1x02_P2.54mm_Horizontal,
2x3 2.54mm IDC Connectors,J8,PinHeader_2x03_P2.54mm_Vertical,
RGB,D1,LED_RGB_5050-6,
1uF,C10,C_0805_2012Metric,
100nF,C6,C_0805_2012Metric,
22uF 6.3V,C4,CP_EIA-3216-18_Kemet-A_Pad1.58x1.35mm_HandSolder,
22uF 6.3V,C3,CP_EIA-3216-18_Kemet-A_Pad1.58x1.35mm_HandSolder,
100nF,C2,C_0805_2012Metric,
100nF,C1,C_0805_2012Metric,
SRD-05VDC-SL-C,K2,RELAY_SRD-05VDC-SL-C,
SRD-05VDC-SL-C,K1,RELAY_SRD-05VDC-SL-C,
ScrewTerminal,J7,Terminal-Block_3.81_4P_LCSC_C395880,
ScrewTerminal,J4,Terminal-Block_3.81_4P_LCSC_C395880,
ScrewTerminal3Pin,J3,Terminal-Block_5.0mm_3P-LCSC_C395850,
ScrewTerminal3Pin,J2,Terminal-Block_5.0mm_3P-LCSC_C395850,
ScrewTerminal,J1,Terminal-Block_3.81_4P_LCSC_C395880,

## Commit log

2023-09-22 prismatic diyBMS boards for LF230 / LF280 cells

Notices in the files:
ControllerCircuit/ControllerCircuit.kicad_pcb:
©2019 to 2023 Stuart Pittaway
ModuleV450/ModuleV450.kicad_pcb:
©2019-2022
